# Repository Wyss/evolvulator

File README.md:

## Evolvulator readme

Server dependencies include: Python 2.7, Twisted, autobahn.websocket, and Flask

### Bioreactor setup

1. Connect small quick release tube to the stop cock of the media reservoirs and attach with a zip tie.
2. Connect bioreactor feeder tube to fresh media reservoir.
3. Connect bioreactor waste tube to waste reservoir.
4. Connect equalizer tubing between waste and fresh media reservoirs.
5. Tape equalizer tubing to the side of media reservoir.
6. Tighten all ports on the top of bioreactor.
7. Fill bioreactor by opening media reservoir stop cock.
8. Once full place feeder tube into the pinch valve.
9. Check that feeder tubing is completely in the valve and make sure all connector tops on the top of the bioreactor are tight!

### Setting up the server:

Create a new database file:

1. navigate to `<repository_path>/code/service/experimentcore`
2. run python
3. type “from exp_dbifc import createDB” without quotes
4. type “createDB(“/location/of/created/database/file_name.DB”)” don't type outside-most quotes
a) replace /location/of/created/database/ with the path to the directory where the database will be created
b) replace file_name with the name of the database.
c) e.g. /home/wade/Documents/Evolvulator/database/Wade.DB

start the server with the following command:

    twistd -noy app.tac

To output information displayed in the terminal to a log file initiate the server with the following command:

    twistd -noy app.tac | tee logfile.txt or twistd -noy app.tac > logfile.txt

### Creating an experiment

Create a `*_evo.json` file for each Evolvulator hardware you would like to run in
`<repository_path>/code/service/evolvulator`

Use the evo_example_evo.json as a template

### Starting the server:

1. cd to `<repository_path>/code/service`

2. start server with `twistd -noy app.tac > date_log.txt`

3. open localhost:8080 in your preferred browser

4. open new tabs for Evo evo

### Running an experiment

1. After filling each bioreactor with clean media, turn on the stir bar, and change the max sensor reading (blank) on the control web page with the strip chart.  You can determine the max sensor reading by opening a web page of each Evolvulator IP and looking at Analog 2.  Refresh a couple times to get accurate reading.

2. On the control web page hit the “Start” button to begin recording data to database.  Hit “Loop” to start control loop.

3. After experiment is complete, copy and rename the Wade.DB files to save all data.

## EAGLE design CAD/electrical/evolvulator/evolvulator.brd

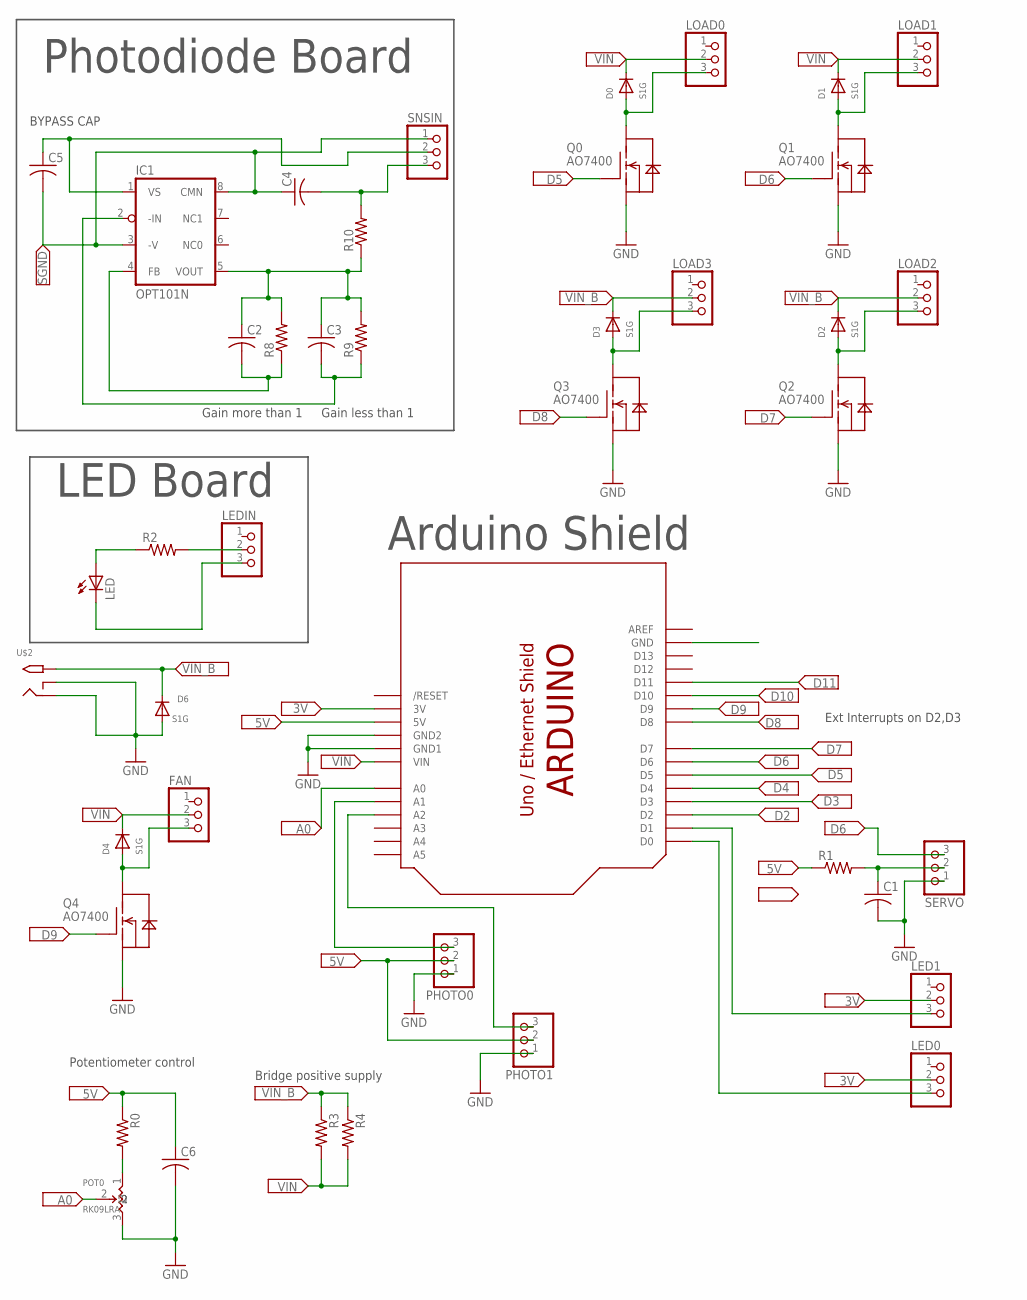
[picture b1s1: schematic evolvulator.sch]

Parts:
C1, C2, C3, C4, C5, C6: C_US; C0603
D0, D1, D2, D3, D4, D6: S1G; SMA_DIODE
FAN: PINHD-1X3; 1X03
IC1: OPT101N; DIL08-ROUND
LED: LED3MM
LED0, LED1: PINHD-1X3; 1X03
LEDIN: PINHD-1X3NB; 1X03_NB
LOAD0, LOAD1, LOAD2, LOAD3: PINHD-1X3; 1X03
PHOTO0, PHOTO1: PINHD-1X3; 1X03
POT0: RK09LRA; ALPS_POT_9MM_RA
Q0, Q1, Q2, Q3, Q4: AO7400; SOT23_FET
R0, R1, R2, R3, R4, R8, R9, R10: R_US; M0805
SERVO: PINHD-1X3; 1X03
SNSIN: PINHD-1X3NB; 1X03_NB
U$1: ARDUINOMAX; ARDUINOSHIELD-MAX
U$2: 2.1MMJACKTHM; PJ-102A

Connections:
3V: LED0.2, LED1.2, U$1.3V
5V: C6.1, PHOTO0.2, PHOTO1.2, R0.1, R1.1, U$1.5V
A0: POT0.2, U$1.A0
D2: U$1.D2
D3: U$1.D3
D4: U$1.D4
D5: Q0.G, U$1.D5
D6: Q1.G, SERVO.3, U$1.D6
D7: Q2.G, U$1.D7
D8: Q3.G, U$1.D8
D9: Q4.G, U$1.D9
D10: U$1.D10
D11: U$1.D11
D222: D3.A, LOAD3.3, Q3.D
GND: C1.2, C6.2, D6.A, PHOTO0.1, PHOTO1.1, POT0.3, Q0.S, Q1.S, Q2.S, Q3.S, Q4.S, SERVO.1, U$1.GND1, U$1.GND2, U$2.RING, U$2.RING_SW
unnamed: C1.1, R1.2, SERVO.2
unnamed: PHOTO0.3, U$1.A1
unnamed: LED1.3, U$1.D1
unnamed: D4.A, FAN.3, Q4.D
unnamed: LED0.3, U$1.D0
unnamed: POT0.1, R0.2
unnamed: C3.2, IC1.2 (-IN), R9.1
unnamed: LEDIN.2, R2.2
unnamed: C2.1, C3.1, IC1.5 (VOUT), R8.2, R9.2, R10.1
unnamed: C2.2, IC1.4 (FB), R8.1
unnamed: C5.1, IC1.1 (VS), SNSIN.2
unnamed: LED.A, R2.1
unnamed: LED.K (C), LEDIN.3
unnamed: PHOTO1.3, U$1.A2
unnamed: C4.2, R10.2, SNSIN.3
unnamed: D0.A, LOAD0.3, Q0.D
unnamed: D1.A, LOAD1.3, Q1.D
unnamed: D2.A, LOAD2.3, Q2.D
SGND: C4.1, C5.2, IC1.3 (-V), IC1.8 (CMN), SNSIN.1
VIN: D0.C, D1.C, D4.C, FAN.2, LOAD0.2, LOAD1.2, R3.2, R4.2, U$1.VIN
VIN_B: D2.C, D3.C, D6.C, LOAD2.2, LOAD3.2, R3.1, R4.1, U$2.TIP

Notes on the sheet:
BYPASS CAP
Gain less than 1
Gain more than 1
Photodiode Board
LED Board
Arduino Shield
Ext Interrupts on D2,D3
Bridge positive supply
Potentiometer control

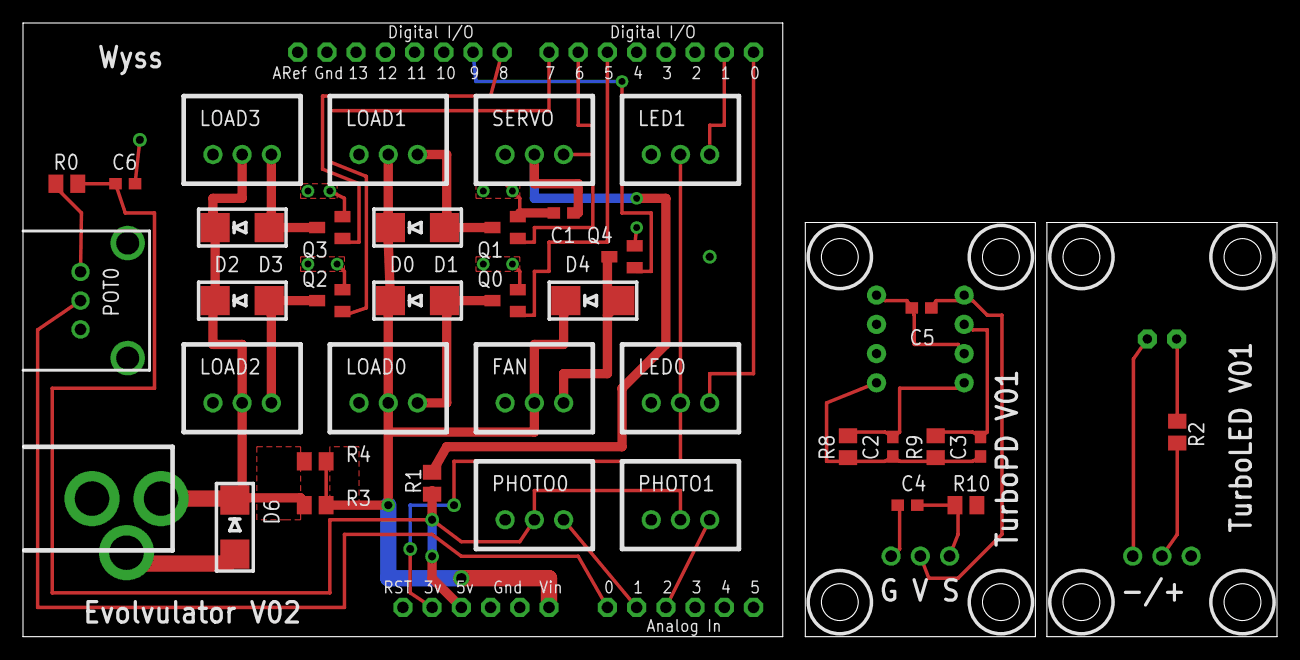
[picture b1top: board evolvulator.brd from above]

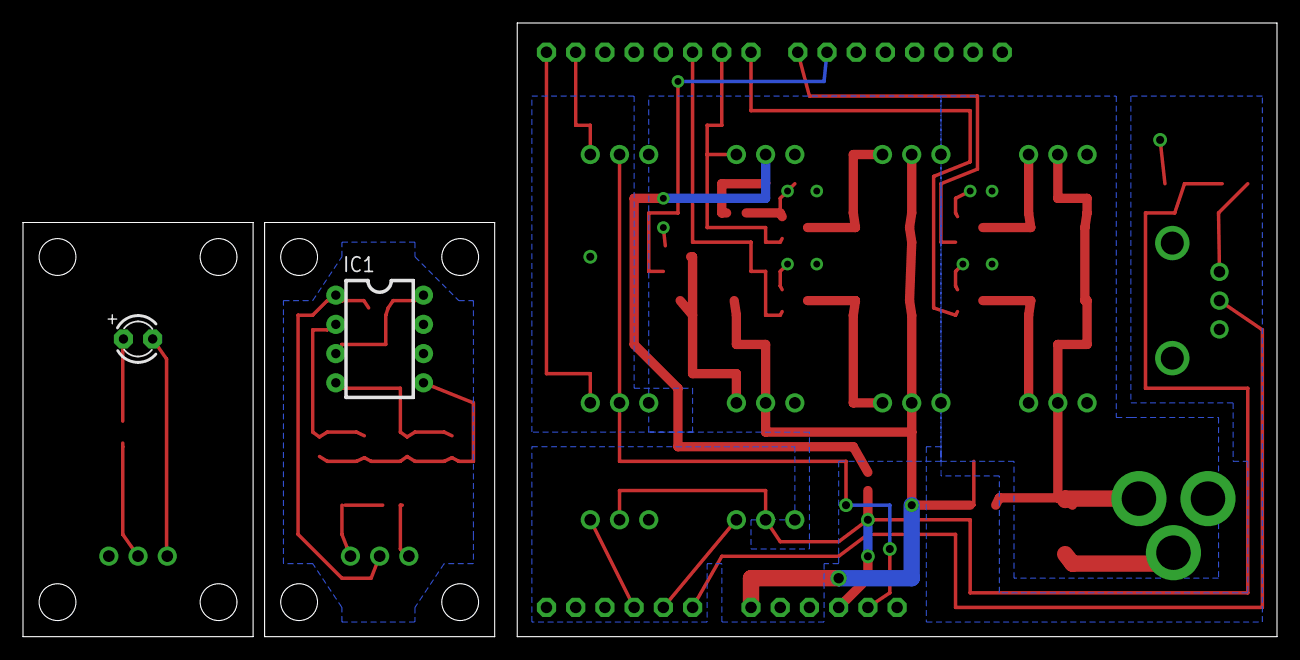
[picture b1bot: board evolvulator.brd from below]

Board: 2 copper layers, 109.0 x 53.3 mm, 42 parts (3 on the bottom side), 31 nets.

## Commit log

2015-10-19 removed errant file
